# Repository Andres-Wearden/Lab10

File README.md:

## 0 Repository Structure

The typical explanation for the repo structure. Lab specific instructions can be
found further below.

### 0.1 HW

The `hw` folder should contain your schematic and board files for your PCB or
circuits. In labs 1-5 and 10, you will be creating schematics for your circuit
in KiCad. 

### 0.2 SW

The `sw` folder should contain your application firmware and software written
for the lab. The `sw/inc` folder contains firmware drivers written for you by
Professor Valvano. Feel free to write your own (in fact, in some labs, you may
be required to write your own).

You can place any other source files in the `sw` folder. TAs will look at the
files you create and/or modify for software quality and for running your
project.

### 0.3 Resources

A couple files are provided in the Resources folder so you don't have to keep
searching for that one TI document. Some of them are immediately useful, like
the TM4C datasheet. Others may be useful for your final project, like the
TM4C_System_Design_Guidelines page.

### 0.4 Git and Github

We will extensively use Git and Github for managing lab projects. This makes it
easier for TAs to grade and help debug the project by allowing us to see commit
histories, maintain a common project structure, and likewise, it makes it easier
for students to collaborate with partners, merge different codebases, and to
debug their work by having a history of commits.

Two common ways of using Git and Github are [Github Desktop](https://desktop.github.com/) and the [command line](https://git-scm.com/downloads).
[Tutorials](https://dev.to/mollynem/git-github--workflow-fundamentals-5496) are also abundant on the net for you to peruse. We've provided a cheatsheet for git
in the Resources folder.

It is highly recommended to make the most out of Git, even if you've never used
it before. Version control will save you a lot of suffering, and tools like Git
or SVN are ubiquitous in the industry.

A gitignore file is added to the root of this repo that may prevent specific
files from being tagged to the repo. This are typically autogenerated output
files we don't care about, but sometimes other stuff (like .lib files) falls
through that we want. Feel free to modify if necessary.

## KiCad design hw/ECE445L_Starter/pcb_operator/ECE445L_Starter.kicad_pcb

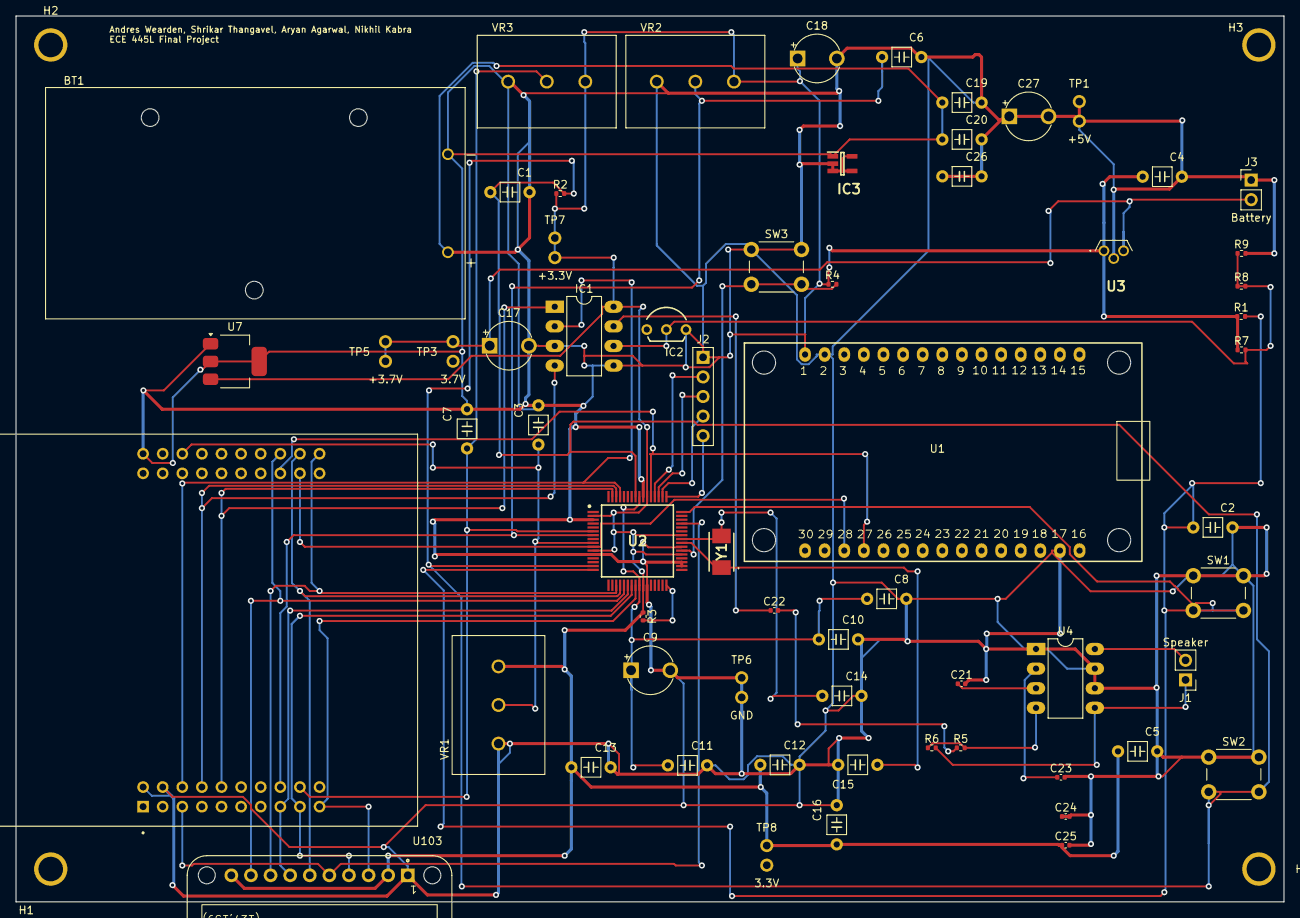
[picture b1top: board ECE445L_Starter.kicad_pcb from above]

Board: 2 copper layers, 164.2 x 114.8 mm, 67 parts (0 on the bottom side), 39 nets.

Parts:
BT1: BH9VPC; BAT_BH9VPC
C1, C2: C; C_Axial_200mil
C3, C5, C6, C7, C10, C11, C12: 0.1uF; C_Axial_200mil
C4, C13: 0.01uF; C_Axial_200mil
C8, C16: 1uF; C_Axial_200mil
C9: 2.2uF; CP_Radial_Tantal200mil
C14, C15: 10pF C0G; C_Axial_200mil
C17, C18, C27: 4.7uF; CP_Radial_Tantal200mil
C19, C20, C26: 1u; C_Axial_200mil
C21: 1uF; C_0402_1005Metric
C22, C24, C25: 100nF; C_0402_1005Metric
C23: 4.7uF; C_0402_1005Metric
H1, H2, H3, H4: MountingHole_4_40
IC1: TLV5616; DIP-8_W7.62mm_LongPads
IC2: LM4041CILPR; ti_LM4041CILPR
IC3: MCP1755T-5002E_OT; SOT95P270X145-5N
J1: Speaker; PinHeader_1x02_P2.54mm_Vertical
J2: JTAG; PinHeader_1x05_P2.54mm_Vertical
J3: Battery; PinHeader_1x02_P2.54mm_Vertical
R1, R2: 10K; R_0402_1005Metric
R3: 1M; R_0402_1005Metric
R4: 10k; R_0402_1005Metric
R5: 20k; R_0402_1005Metric
R6: 110k; R_0402_1005Metric
R7: 500; R_0402_1005Metric
R8: 10.3k; R_0402_1005Metric
R9: 1.425k; R_0402_1005Metric
SW1: UP; SW_PUSH_6mm
SW2: DOWN; SW_PUSH_6mm
SW3: Reset; SW_PUSH_6mm
TP1: +5V; Testpoint_1x02_P2.54mm
TP3: 3.7V; Testpoint_1x02_P2.54mm
TP5: +3.7V; Testpoint_1x02_P2.54mm
TP6: GND; Testpoint_1x02_P2.54mm
TP7: +3.3V; Testpoint_1x02_P2.54mm
TP8: 3.3V; Testpoint_1x02_P2.54mm
U1: ESP32_30pin
U2: TM4C123GH6PMIR; QFP50P1200X1200X160-64N
U3: LP2950-33LPRE3; TL431CLPM
U4: MCP34119P; DIP-8_W7.62mm_LongPads
U5: EK-TM4C123GXL; ti_EKTM4C123GXL
U7: LM2937xMP; SOT-223-3_TabPin2
U103: Adafruit ST7735R; adafruit_st7735r2
VR1, VR2, VR3: P160KN-0QC15B500K; P160
Y1: ABM3-16.000MHZ-B2-T; ABM3

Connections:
+3V3: C4.1, C5.1, C12.1, C13.1, C16.1, C18.1, C25.1, IC1.8 (VDD), R1.1, R2.1, R3.1, R4.1, R7.1, TP7.1 (A), TP7.2 (B), TP8.1, U1.1 (VIN), U2.2 (VDDA), U2.11 (VDD_1), U2.26 (VDD_2), U2.37 (VBAT), U2.42 (VDD_3), U2.54 (VDD_4), U3.1 (OUTPUT), U7.3 (VO), U103.2 (VCC), U103.10 (LITE), VR1.3, VR2.3, VR3.3
+5V: C17.2, C18.2, C20.2, C24.2, C26.1, C26.2, C27.1, C27.2, IC3.5 (VOUT), J3.1 (A), TP1.1 (A), TP1.2 (B), TP6.1 (A), TP6.2 (B), U3.2 (GND), U4.6 (Vcc), U5.J3_1 (+VBUS), U7.1 (VI)
/12V: BT1.+, C19.1, IC3.1 (VIN), IC3.3 (~SHDN)
/+3_7V: C17.1, J3.2 (B), TP3.1, TP5.1 (A), TP5.2 (B), U3.3 (INPUT)
/LDO: C8.1, C9.1, C10.1, C11.1, U2.25 (VDDC_1), U2.56 (VDDC_2)
/OSC1: C14.1, U2.41 (OSC1), Y1.2
/OSC2: C15.1, U2.40 (OSC0), Y1.1
/Reset: R4.2, SW3.2, U2.38 (~RST)
/TCK: J2.2 (B), U2.52 (PC0/TCK/SWCLK)
/TDI: J2.4 (C), U2.50 (PC2/TDI)
/TDO: J2.5 (C), U2.49 (PC3/TDO/SWO)
/TMS: J2.3 (C), U2.51 (PC1/TMS/SWDIO)
DAC_Out: C22.1, IC1.7 (OUT)
GND: BT1.-, C1.2, C2.2, C3.2, C4.2, C5.2, C6.2, C7.2, C8.2, C9.2, C10.2, C11.2, C12.2, C13.2, C14.2, C15.2, C16.2, C19.2, C21.2, C23.2, C24.1, C25.2, IC1.3 (~CS), IC1.5 (AGND), IC2.3, IC3.2 (GND), J2.1 (A), R9.2, SW1.1, SW2.1, SW3.1, U1.2 (GND), U1.17 (GND), U2.3 (GNDA), U2.12 (GND_1), U2.27 (GND_2), U2.34 (XOSC0), U2.35 (GNDX), U2.39 (GND_3), U2.55 (GND_4), U4.1 (CD), U4.7 (GND), U5.J2_1 (GND), U5.J3_2 (GND), U7.2 (GND), U103.1 (GND), VR1.1, VR2.1, VR3.1
unnamed: C22.2, R5.1
unnamed: IC1.6 (REF), IC2.2, R7.2, R8.1, R8.2, R9.1
unnamed: R3.2, U2.32 (~WAKE)
unnamed: C21.1, U4.3 (FC1)
unnamed: C23.1, U4.2 (FC2)
unnamed: R5.2, R6.1, U4.4 (VIN)
unnamed: J1.1, R6.2, U4.5 (VO1)
unnamed: J1.2, U4.8 (VO2)
PA2: U2.19 (PA2/SSI0C1K), U5.J2_10 (PA2), U103.8 (SCK)
PA3: U2.20 (PA3/SSI0FSS), U5.J2_9 (PA3), U103.6 (TFT_CS)
PA4: U2.21 (PA4/SSI0RX), U5.J2_8 (PA4), U103.9 (MISO)
PA5: U2.22 (PA5/SSI0TX), U5.J1_8 (PA5), U103.7 (MOSI)
PA6: U2.23 (PA6), U5.J1_9 (PA6), U103.4 (D/C)
PA7: U2.24 (PA7), U5.J1_10 (PA7), U103.3 (RESET)
PB0: U2.45 (PB0/USB0ID), U5.J1_3 (PB0), U103.5 (CARD_CS)
PB3: C2.1, R1.2, SW1.2, U2.48 (PB3/I2C0SDA)
PB5: C1.1, R2.2, SW2.2, U2.57 (PB5)
PD0: IC1.2 (SCLK), U2.61 (PD0), U5.J3_3 (PD0)
PD1: IC1.4 (FS), U2.62 (PD1), U5.J3_4 (PD1)
PD2: IC1.1 (DIN), U2.63 (PD2), U5.J3_5 (PD2)
PD6: U1.27 (GPIO3), U2.53 (PD6), U5.J4_8 (PD6)
PD7: U1.28 (GPIO1), U2.10 (PD7), U5.J4_9 (PD7)
PE0: C3.1, U2.9 (PE0), U5.J2_3 (PE0), VR1.2
PE2: C6.1, U2.7 (PE2), U5.J3_8 (PE2), VR2.2
PE3: C7.1, U2.6 (PE3), U5.J3_9 (PE3), VR3.2

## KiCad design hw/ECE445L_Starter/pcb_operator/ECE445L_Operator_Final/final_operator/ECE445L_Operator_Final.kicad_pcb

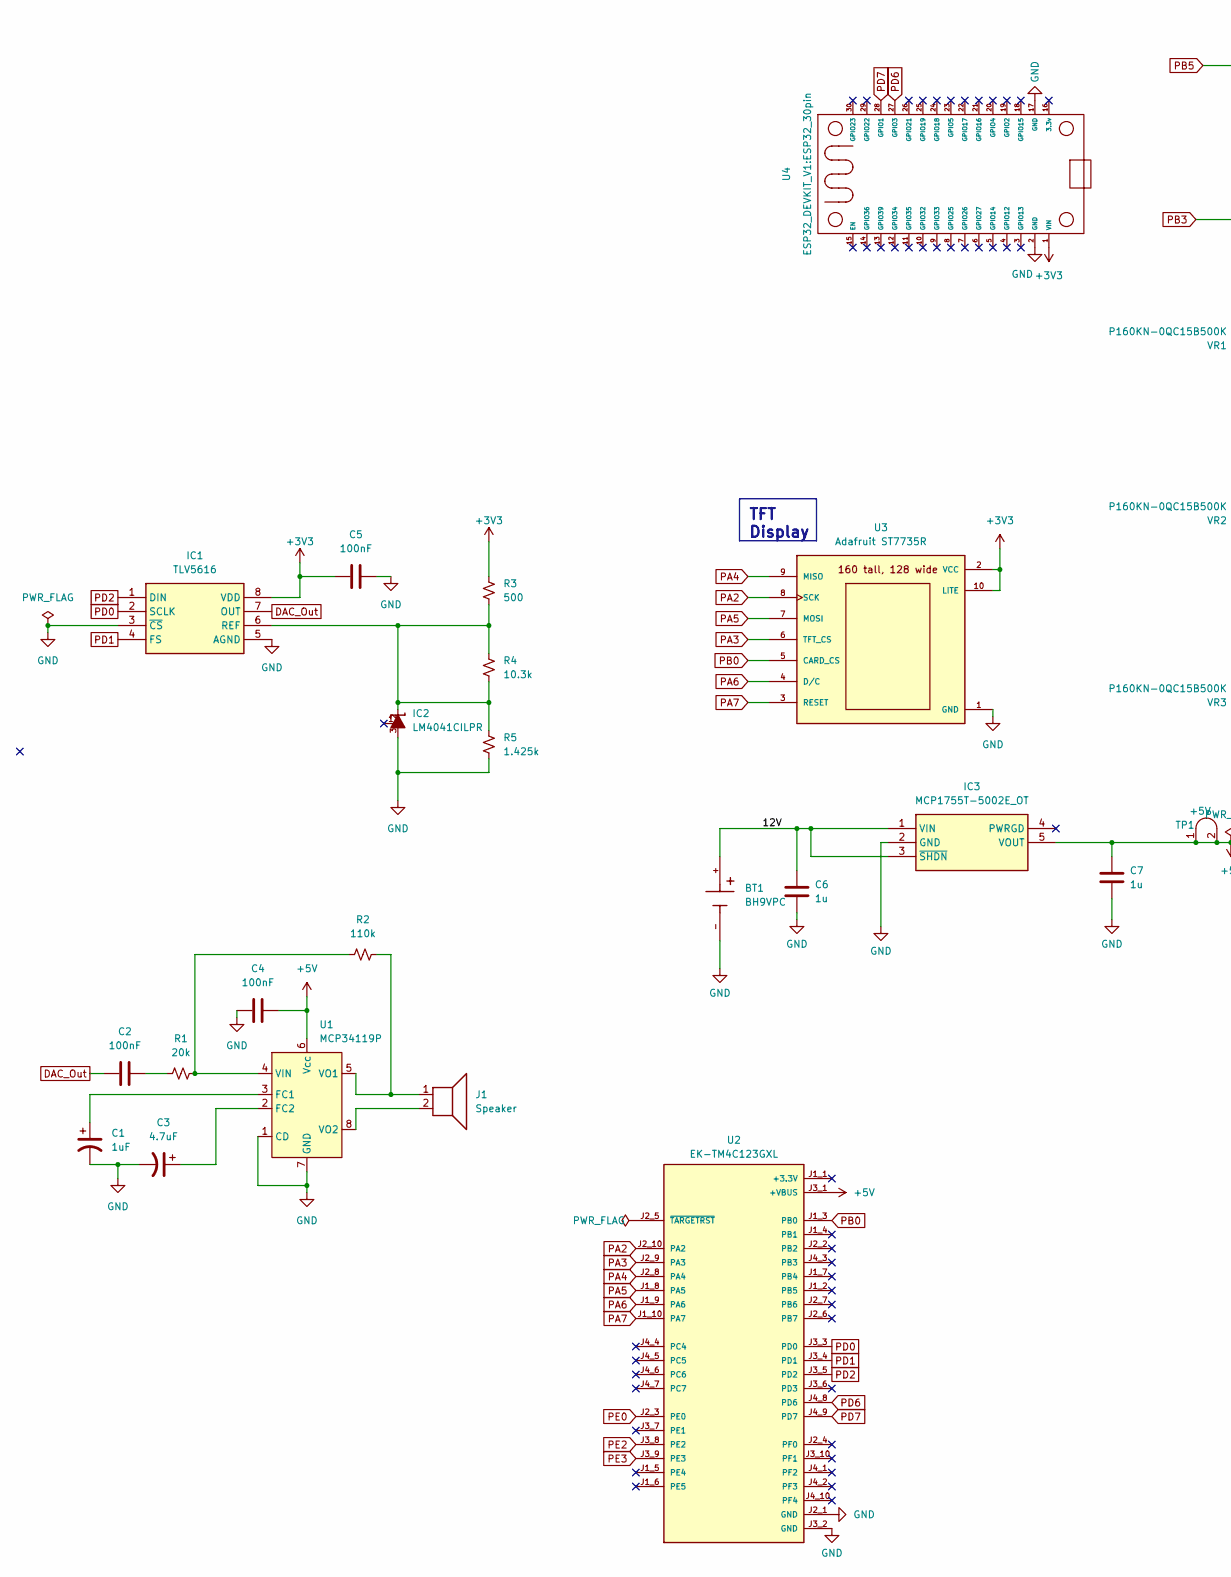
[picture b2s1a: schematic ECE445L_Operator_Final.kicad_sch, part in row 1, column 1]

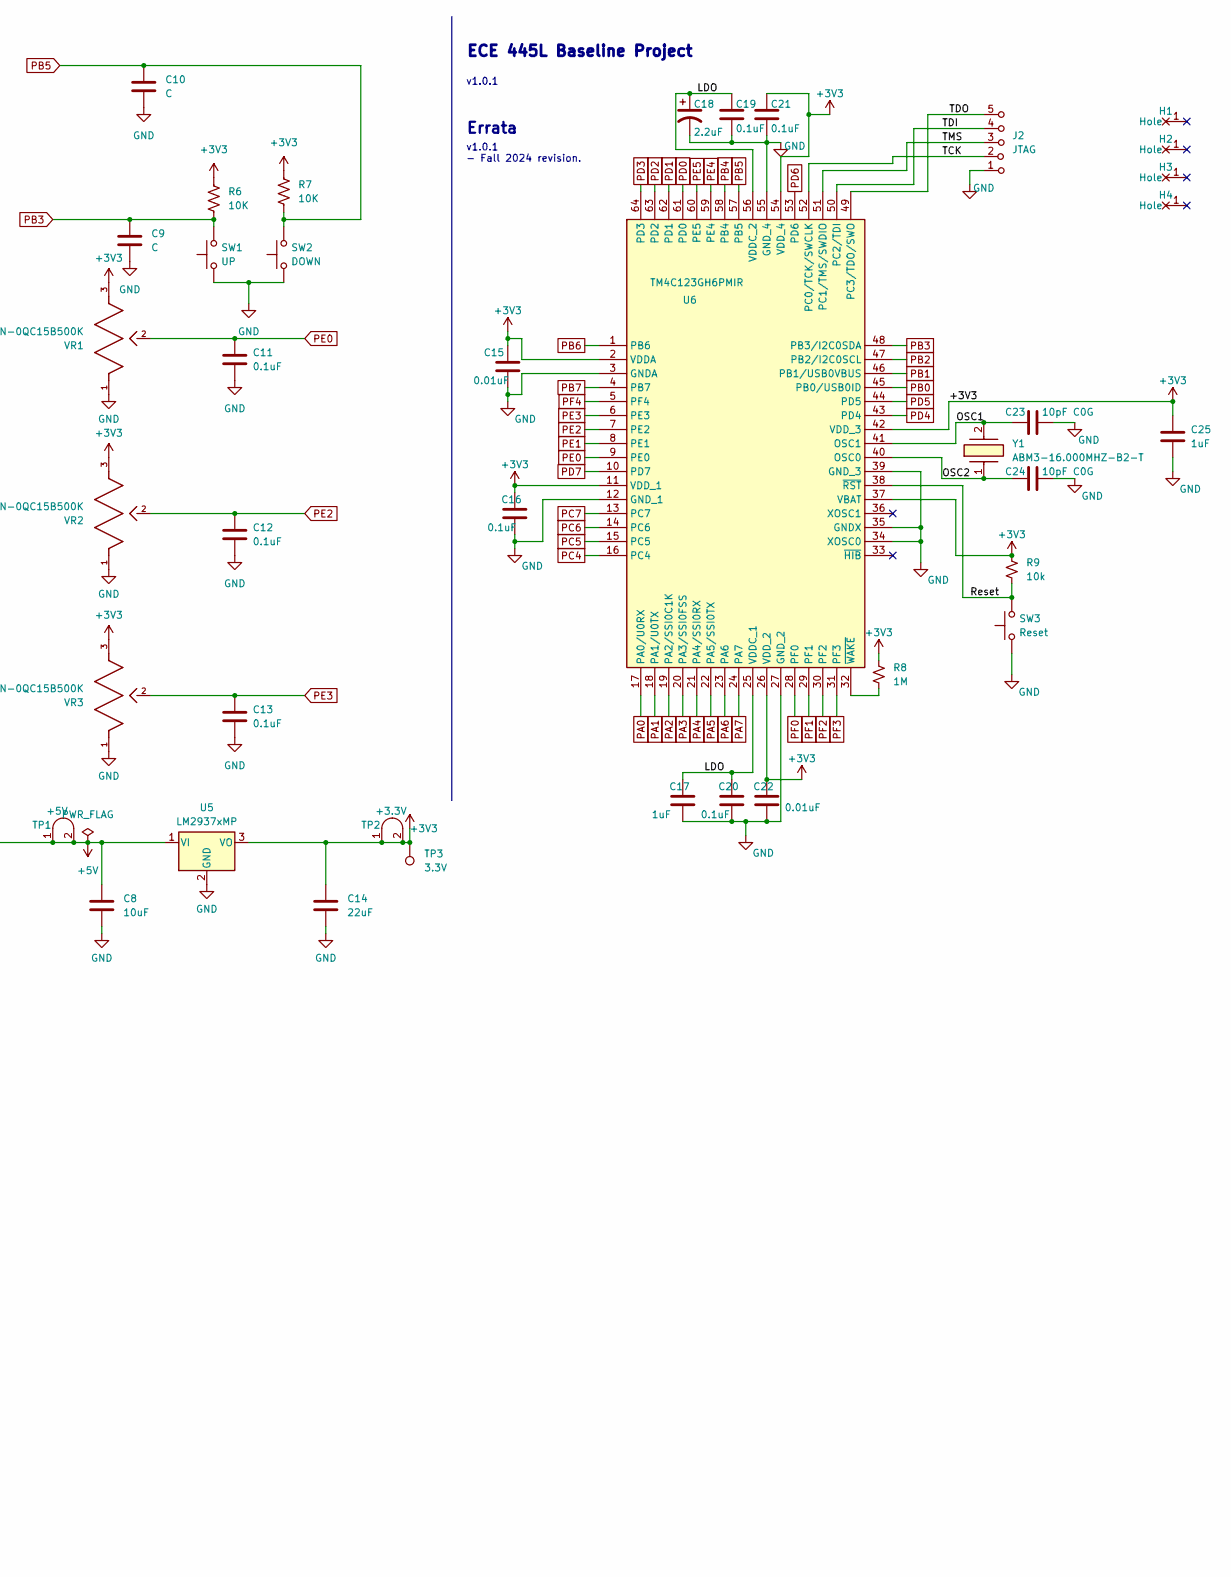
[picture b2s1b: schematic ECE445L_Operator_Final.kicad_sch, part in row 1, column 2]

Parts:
BT1: BH9VPC; BAT_BH9VPC; PARTREV F
C1, C17, C25: 1uF; C_Axial_200mil
C2, C4, C5: 100nF; C_Axial_200mil
C3: 4.7uF; C_Axial_200mil
C6, C7: 1u; C_Axial_200mil
C8: 10uF; C_Axial_200mil
C9, C10: C; C_Axial_200mil
C11, C12, C13, C16, C19, C20, C21: 0.1uF; C_Axial_200mil
C14: 22uF; C_Axial_200mil
C15, C22: 0.01uF; C_Axial_200mil
C18: 2.2uF; C_Axial_200mil
C23, C24: 10pF C0G; C_Axial_200mil
H1, H2, H3, H4: MountingHole_4_40
IC1: TLV5616; DIP-8_W7.62mm_LongPads
IC2: LM4041CILPR; ti_LM4041CILPR
IC3: MCP1755T-5002E_OT; SOT95P270X145-5N; Mouser Part Number 579-MCP1755T-5002EOT
J1: Speaker; PinHeader_1x02_P2.54mm_Vertical
J2: JTAG; PinHeader_1x05_P2.54mm_Vertical
R1: 20k; R_0805_2012Metric
R2: 110k; R_0805_2012Metric
R3: 500; R_0805_2012Metric
R4: 10.3k; R_0805_2012Metric
R5: 1.425k; R_0805_2012Metric
R6, R7: 10K; R_0805_2012Metric
R8: 1M; R_0805_2012Metric
R9: 10k; R_0805_2012Metric
SW1: UP; SW_PUSH_6mm
SW2: DOWN; SW_PUSH_6mm
SW3: Reset; SW_PUSH_6mm
TP1: +5V; Testpoint_1x02_P2.54mm
TP2: +3.3V; Testpoint_1x02_P2.54mm
TP3: 3.3V; Testpoint_1x02_P2.54mm
U1: MCP34119P; DIP-8_W7.62mm_LongPads
U2: EK-TM4C123GXL; ti_EKTM4C123GXL
U3: Adafruit ST7735R; adafruit_st7735r2
U4: ESP32_30pin
U5: LM2937xMP; SOT-223-3_TabPin2
U6: TM4C123GH6PMIR; QFP50P1200X1200X160-64N; Mouser Part Number 595-TM4C123GH6PMIR
VR1: P160KN-0QC15B500K; P160; PARTNO 987-1304-ND
VR2, VR3: P160KN-0QC15B500K; PinHeader_1x03_P2.54mm_Vertical; PARTNO 987-1304-ND
Y1: ABM3-16.000MHZ-B2-T; ABM3; Mouser Part Number 815-ABM3-16-B2-T

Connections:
+3V3: C5.1, C14.1, C15.1, C16.1, C21.1, C22.1, C25.1, IC1.8 (VDD), R3.1, R6.1, R7.1, R8.1, R9.1, TP2.1 (A), TP2.2 (B), TP3.1, U3.2 (VCC), U3.10 (LITE), U4.1 (VIN), U5.3 (VO), U6.2 (VDDA), U6.11 (VDD_1), U6.26 (VDD_2), U6.37 (VBAT), U6.42 (VDD_3), U6.54 (VDD_4), VR1.3, VR2.3, VR3.3
+5V: C4.2, C7.1, C8.1, IC3.5 (VOUT), TP1.1 (A), TP1.2 (B), U1.6 (Vcc), U2.J3_1 (+VBUS), U5.1 (VI)
/12V: BT1.+, C6.1, IC3.1 (VIN), IC3.3 (~SHDN)
/LDO: C17.1, C18.1, C19.1, C20.1, U6.25 (VDDC_1), U6.56 (VDDC_2)
/OSC1: C23.1, U6.41 (OSC1), Y1.2
/OSC2: C24.1, U6.40 (OSC0), Y1.1
/Reset: R9.2, SW3.2, U6.38 (~RST)
/TCK: J2.2 (B), U6.52 (PC0/TCK/SWCLK)
/TDI: J2.4 (C), U6.50 (PC2/TDI)
/TDO: J2.5 (C), U6.49 (PC3/TDO/SWO)
/TMS: J2.3 (C), U6.51 (PC1/TMS/SWDIO)
DAC_Out: C2.1, IC1.7 (OUT)
GND: BT1.-, C1.2, C3.2, C4.1, C5.2, C6.2, C7.2, C8.2, C9.2, C10.2, C11.2, C12.2, C13.2, C14.2, C15.2, C16.2, C17.2, C18.2, C19.2, C20.2, C21.2, C22.2, C23.2, C24.2, C25.2, IC1.3 (~CS), IC1.5 (AGND), IC2.3, IC3.2 (GND), J2.1 (A), R5.2, SW1.1, SW2.1, SW3.1, U1.1 (CD), U1.7 (GND), U2.J2_1 (GND), U2.J3_2 (GND), U3.1 (GND), U4.2 (GND), U4.17 (GND), U5.2 (GND), U6.3 (GNDA), U6.12 (GND_1), U6.27 (GND_2), U6.34 (XOSC0), U6.35 (GNDX), U6.39 (GND_3), U6.55 (GND_4), VR1.1, VR2.1, VR3.1
unnamed: C2.2, R1.1
unnamed: IC1.6 (REF), IC2.2, R3.2, R4.1, R4.2, R5.1
unnamed: C1.1, U1.3 (FC1)
unnamed: C3.1, U1.2 (FC2)
unnamed: R1.2, R2.1, U1.4 (VIN)
unnamed: J1.1, R2.2, U1.5 (VO1)
unnamed: J1.2, U1.8 (VO2)
unnamed: R8.2, U6.32 (~WAKE)
PA0: U6.17 (PA0/U0RX)
PA1: U6.18 (PA1/U0TX)
PA2: U2.J2_10 (PA2), U3.8 (SCK), U6.19 (PA2/SSI0C1K)
PA3: U2.J2_9 (PA3), U3.6 (TFT_CS), U6.20 (PA3/SSI0FSS)
PA4: U2.J2_8 (PA4), U3.9 (MISO), U6.21 (PA4/SSI0RX)
PA5: U2.J1_8 (PA5), U3.7 (MOSI), U6.22 (PA5/SSI0TX)
PA6: U2.J1_9 (PA6), U3.4 (D/C), U6.23 (PA6)
PA7: U2.J1_10 (PA7), U3.3 (RESET), U6.24 (PA7)
PB0: U2.J1_3 (PB0), U3.5 (CARD_CS), U6.45 (PB0/USB0ID)
PB1: U6.46 (PB1/USB0VBUS)
PB2: U6.47 (PB2/I2C0SCL)
PB3: C9.1, R6.2, SW1.2, U6.48 (PB3/I2C0SDA)
PB4: U6.58 (PB4)
PB5: C10.1, R7.2, SW2.2, U6.57 (PB5)
PB6: U6.1 (PB6)
PB7: U6.4 (PB7)
PC4: U6.16 (PC4)
PC5: U6.15 (PC5)
PC6: U6.14 (PC6)
PC7: U6.13 (PC7)
PD0: IC1.2 (SCLK), U2.J3_3 (PD0), U6.61 (PD0)
PD1: IC1.4 (FS), U2.J3_4 (PD1), U6.62 (PD1)
PD2: IC1.1 (DIN), U2.J3_5 (PD2), U6.63 (PD2)
PD3: U6.64 (PD3)
PD4: U6.43 (PD4)
PD5: U6.44 (PD5)
PD6: U2.J4_8 (PD6), U4.27 (GPIO3), U6.53 (PD6)
PD7: U2.J4_9 (PD7), U4.28 (GPIO1), U6.10 (PD7)
PE0: C11.1, U2.J2_3 (PE0), U6.9 (PE0), VR1.2
PE1: U6.8 (PE1)
PE2: C12.1, U2.J3_8 (PE2), U6.7 (PE2), VR2.2
PE3: C13.1, U2.J3_9 (PE3), U6.6 (PE3), VR3.2
PE4: U6.59 (PE4)
PE5: U6.60 (PE5)
PF0: U6.28 (PF0)
PF1: U6.29 (PF1)
PF2: U6.30 (PF2)
PF3: U6.31 (PF3)
PF4: U6.5 (PF4)

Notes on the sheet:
TFT Display
ECE 445L Baseline Project
v1.0.1 - Fall 2024 revision.
v1.0.1
Errata

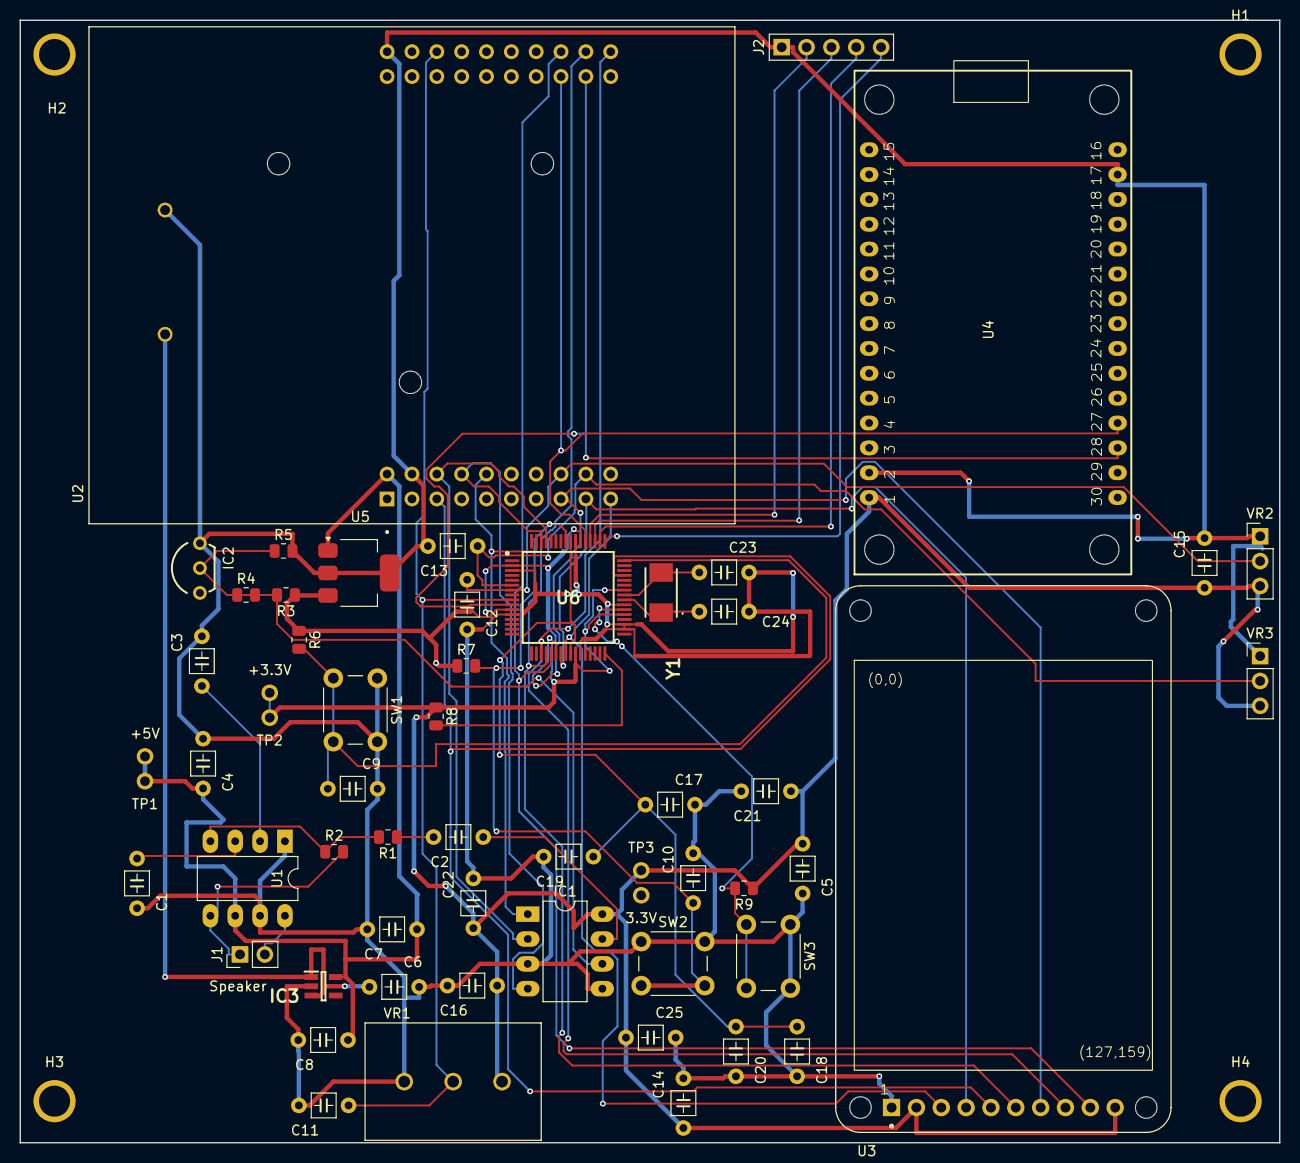
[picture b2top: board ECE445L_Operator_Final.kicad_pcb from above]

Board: 2 copper layers, 128.8 x 114.8 mm, 60 parts (1 on the bottom side), 38 nets.

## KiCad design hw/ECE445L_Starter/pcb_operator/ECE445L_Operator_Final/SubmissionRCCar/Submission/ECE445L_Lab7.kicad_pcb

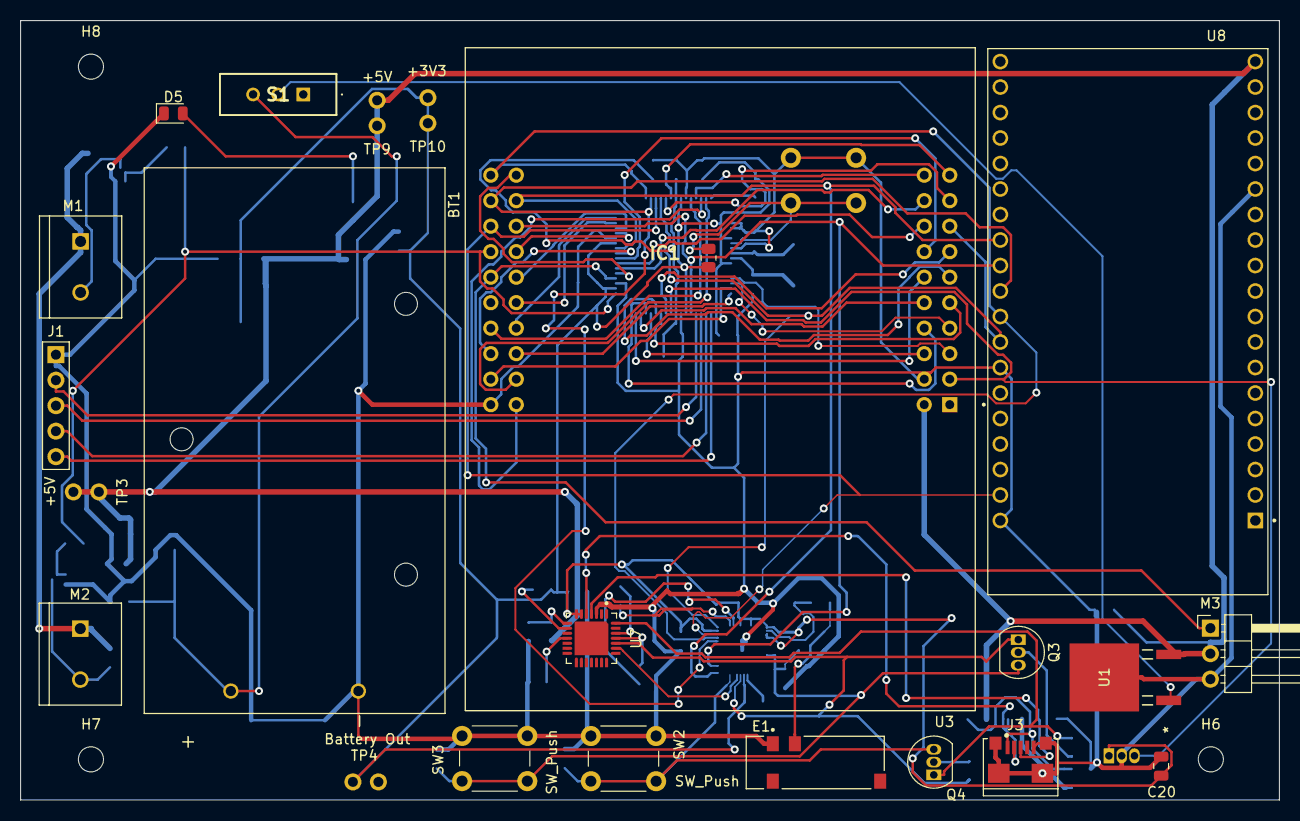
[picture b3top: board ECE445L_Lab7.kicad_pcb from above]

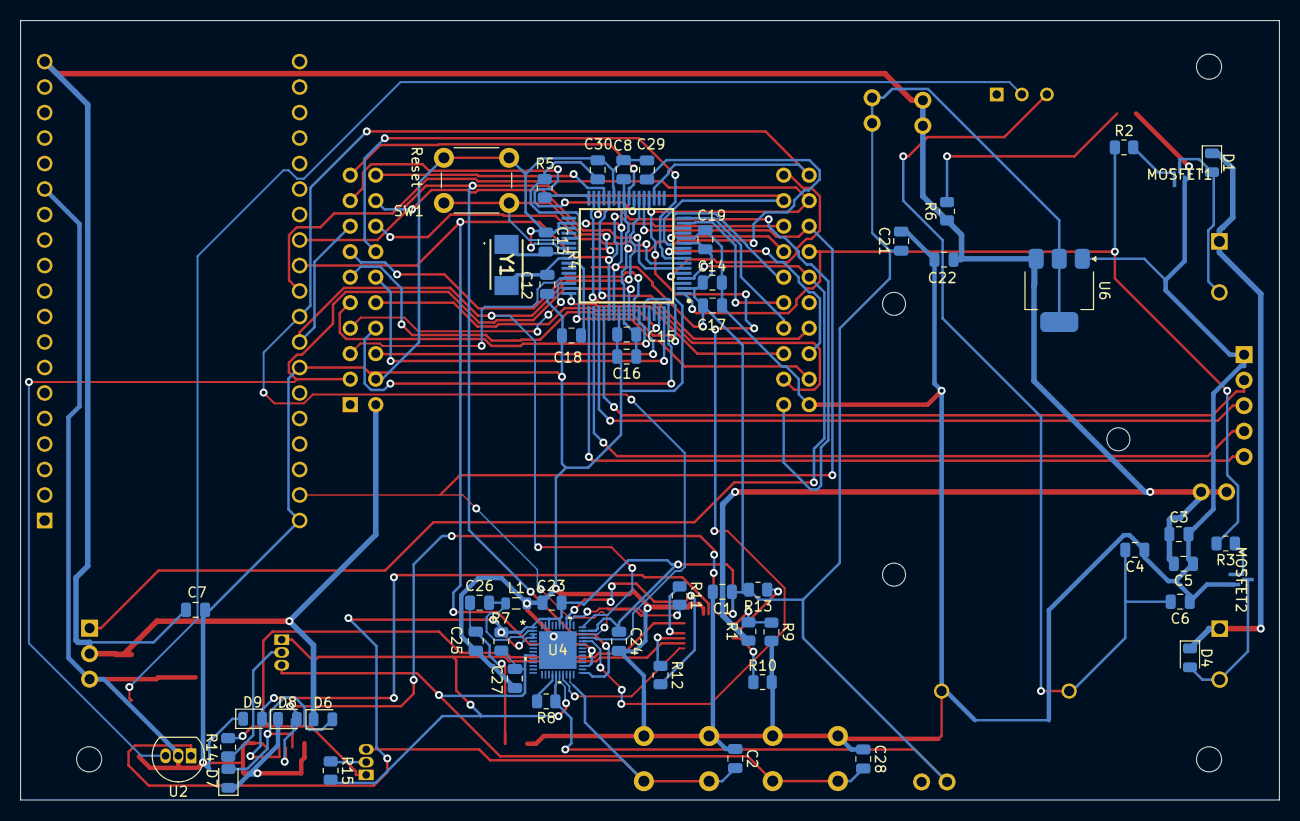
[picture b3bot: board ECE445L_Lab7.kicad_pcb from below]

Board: 2 copper layers, 125.4 x 77.6 mm, 81 parts (55 on the bottom side), 75 nets.

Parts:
BT1: BH9VPC; BAT_BH9VPC
C1, C2, C27, C28: 0.1u; C_0805_2012Metric
C3: 4.7uF; C_0805_2012Metric
C4, C5, C6, C20: 1u; C_0805_2012Metric
C7, C21, C22, C23, C24: 10u; C_0805_2012Metric
C8: 2.2uF; C_0805_2012Metric
C12, C13: 10pF COG; C_0805_2012Metric
C14, C15: 1uF; C_0805_2012Metric
C16, C19, C29, C30: 0.1uF; C_0805_2012Metric
C17, C18: 0.01uF; C_0805_2012Metric
C25: 2.7p; C_0805_2012Metric
C26: 4.7p; C_0805_2012Metric
D1, D4, D6: D; D_0805_2012Metric
D5: LED; LED_0805_2012Metric
D7, D8, D9: D_TVS; D_0805_2012Metric
E1: PRO-OB-440; XDCR_PRO-OB-440
H6, H7, H8: MountingHole_2.5mm
IC1: TM4C123GH6PMIR; QFP50P1200X1200X160-64N
J1: JTAG; PinHeader_1x05_P2.54mm_Vertical
J3: DX4R005HJ5R2000; JAE_DX4R005HJ5R2000
L1: 1.6n; L_0805_2012Metric
M1, M2: Motor_DC; TE_282837-2
M3: Motor_Servo; PinHeader_1x03_P2.54mm_Horizontal
MOSFET1, MOSFET2: SSM3K56FS_LF; SSM_TOS
Q3, Q4: S8050; TO-92_Inline
R1: 22.1k; R_0805_2012Metric
R2, R3, R11, R12: 1k; R_0805_2012Metric
R4, R7, R8, R10, R14, R15: 10k; R_0805_2012Metric
R5: 1M; R_0805_2012Metric
R6, R13: 2k; R_0805_2012Metric
R9: 47.5k; R_0805_2012Metric
S1: SLW-116641-5A-S-D; SLW1166415ASD
SW1: Reset; SW_PUSH_6mm
SW2, SW3: SW_Push; SW_PUSH_6mm
TP3, TP9: +5V; Testpoint_1x02_P2.54mm
TP4: Battery Out; Testpoint_1x02_P2.54mm
TP10: +3V3; Testpoint_1x02_P2.54mm
U1: NCV7805BDTRKG; DPAK-3_ONS
U2: DRV5055A2xLPGxQ1; TO-92_Inline
U3: EK-TM4C123GXL; ti_EKTM4C123GXL
U4: ESP32-D0WD-V3; QFN48_ESP32-D0WD-V3_EXP
U6: AMS1117; SOT-223-3_TabPin2
U7: CP2102N-A02-GQFN28R; IC_CP2102N-A02-GQFN28R
U8: ESP32-DEVKITC-32D; MODULE_ESP32-DEVKITC-32D
Y1: ABM3-16.000MHZ-B2-T; ABM3

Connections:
+5V: C3.1, C5.2, C7.1, C22.1, D6.1 (K), M3.2 (+), R1.1, R6.1, TP3.1 (A), TP3.2 (B), TP9.1 (A), TP9.2 (B), U1.3 (OUTPUT), U3.J3_1 (+VBUS), U6.3 (VI), U8.J2-19 (EXT_5V)
+9V: D1.1 (K), D4.1 (K), M1.1 (+), M2.1 (+)
/Lab7_microcontroller/LDO: C8.1, C15.1, C16.1, C29.1, IC1.25 (VDDC_1), IC1.56 (VDDC_2)
/Lab7_microcontroller/OSC1: C12.1, IC1.41 (OSC1), Y1.2
/Lab7_microcontroller/OSC2: C13.1, IC1.40 (OSC0), Y1.1
/Lab7_microcontroller/Reset: IC1.38 (~RST), R4.2, SW1.2
/Lab7_microcontroller/TCK: IC1.52 (PC0/TCK/SWCLK), J1.2 (B)
/Lab7_microcontroller/TDI: IC1.50 (PC2/TDI), J1.4 (C)
/Lab7_microcontroller/TDO: IC1.49 (PC3/TDO/SWO), J1.5 (C)
/Lab7_microcontroller/TMS: IC1.51 (PC1/TMS/SWDIO), J1.3 (C)
/Lab7_power/+9V: BT1.+, C4.2, C6.2, S1.3 (NO)
CTS: U4.21 (MTDO), U7.23 (CTS)
DTR: Q4.1 (E), R14.2, U7.28 (DTR)
EN: C27.1, C28.2, Q3.3 (C), R7.2, SW3.2, U4.9 (CHIP_PU)
GND: BT1.-, C1.2, C2.1, C3.2, C4.1, C5.1, C6.1, C7.2, C8.2, C12.2, C13.2, C14.2, C15.2, C16.2, C17.2, C18.2, C19.2, C20.2, C21.2, C22.2, C23.2, C24.2, C25.2, C27.2, C28.1, C29.2, C30.2, D5.1 (K), D7.1 (A1), D8.1 (A1), D9.1 (A1), E1.1, IC1.3 (GNDA), IC1.12 (GND_1), IC1.27 (GND_2), IC1.34 (XOSC0), IC1.35 (GNDX), IC1.39 (GND_3), IC1.55 (GND_4), J1.1 (A), J3.5 (GND), J3.SH1 (SHIELD), J3.SH2 (SHIELD__1), J3.SH3 (SHIELD__2), J3.SH4 (SHIELD__3), L1.2, M3.3 (-), MOSFET1.2, MOSFET2.2, R9.2, R10.2, SW1.1, SW2.1, SW3.1, U1.2 (GROUND), U2.2 (GND), U3.J2_1 (GND), U3.J3_2 (GND), U4.49 (GND), U6.1 (ADJ), U7.3 (GND), U8.J2-14 (GND1), U8.J3-1 (GND3), U8.J3-7 (GND2)
IO0: C2.2, Q4.3 (C), SW2.2, U4.23 (GPIO0)
unnamed: C25.1, C26.1, E1.2
unnamed: D1.2 (A), M1.2 (-), MOSFET1.3
unnamed: D4.2 (A), M2.2 (-), MOSFET2.3
unnamed: D5.2 (A), R6.2
unnamed: D6.2 (A), D7.2 (A2), J3.1 (VBUS)
unnamed: IC1.32 (~WAKE), R5.2
unnamed: MOSFET1.1, R2.2
unnamed: MOSFET2.1, R3.1
unnamed: Q3.2 (B), R14.1
unnamed: Q4.2 (B), R15.1
unnamed: S1.2 (COM), U1.1 (INPUT)
unnamed: C26.2, L1.1, U4.2 (LNA_IN)
unnamed: R8.2, U4.18 (MTDI)
unnamed: R12.1, U7.25 (RXD)
unnamed: R11.1, U7.26 (TXD)
unnamed: R1.2, R9.1, U7.8 (VBUS)
unnamed: R13.1, U7.9 (~RST)
unnamed: R10.1, U7.11 (~SUSPEND)
PA2: IC1.19 (PA2/SSI0C1K), U3.J2_10 (PA2), U4.35 (GPIO18), U8.J3-9 (IO18)
PA3: IC1.20 (PA3/SSI0FSS), U3.J2_9 (PA3), U4.34 (GPIO5), U8.J3-10 (IO5)
PA4: IC1.21 (PA4/SSI0RX), U3.J2_8 (PA4), U4.36 (GPIO23), U8.J3-2 (IO23)
PA5: IC1.22 (PA5/SSI0TX), U3.J1_8 (PA5), U4.38 (GPIO19), U8.J3-8 (IO19)
PA6: IC1.23 (PA6), U3.J1_9 (PA6)
PA7: IC1.24 (PA7), U3.J1_10 (PA7)
PB0: IC1.45 (PB0/USB0ID), U3.J1_3 (PB0)
PB1: IC1.46 (PB1/USB0VBUS), U3.J1_4 (PB1)
PB2: IC1.47 (PB2/I2C0SCL), U3.J2_2 (PB2)
PB3: IC1.48 (PB3/I2C0SDA), U3.J4_3 (PB3)
PB4: IC1.58 (PB4), U3.J1_7 (PB4)
PB5: IC1.57 (PB5), U2.3 (OUT), U3.J1_2 (PB5)
PB6: IC1.1 (PB6), R2.1, R3.2, U3.J2_7 (PB6)
PB7: IC1.4 (PB7), M3.1 (PWM), U3.J2_6 (PB7)
PC4: IC1.16 (PC4), U3.J4_4 (PC4)
PC5: IC1.15 (PC5), U3.J4_5 (PC5)
PC6: IC1.14 (PC6), U3.J4_6 (PC6)
PC7: IC1.13 (PC7), U3.J4_7 (PC7)
PD0: IC1.61 (PD0), U3.J3_3 (PD0)
PD1: IC1.62 (PD1), U3.J3_4 (PD1)
PD2: IC1.63 (PD2), U3.J3_5 (PD2)
PD3: IC1.64 (PD3), U3.J3_6 (PD3)
PD6: IC1.53 (PD6), U3.J4_8 (PD6), U4.27 (GPIO17), U8.J3-11 (IO17)
PD7: IC1.10 (PD7), U3.J4_9 (PD7), U4.25 (GPIO16), U8.J3-12 (IO16)
PE0: IC1.9 (PE0), U3.J2_3 (PE0)
PE1: IC1.8 (PE1), U3.J3_7 (PE1)
PE2: IC1.7 (PE2), U3.J3_8 (PE2)
PE3: IC1.6 (PE3), U3.J3_9 (PE3)
PE4: IC1.59 (PE4), U3.J1_5 (PE4)
PE5: IC1.60 (PE5), U3.J1_6 (PE5)
PF0: IC1.28 (PF0), U3.J2_4 (PF0)
PF1: IC1.29 (PF1), U3.J3_10 (PF1)
PF2: IC1.30 (PF2), U3.J4_1 (PF2)
PF3: IC1.31 (PF3), U3.J4_2 (PF3)
PF4: IC1.5 (PF4), U3.J4_10 (PF4)
REGIN: C1.1, C14.1, C17.1, C18.1, C19.1, C20.1, C21.1, C23.1, C24.1, C30.1, IC1.2 (VDDA), IC1.11 (VDD_1), IC1.26 (VDD_2), IC1.37 (VBAT), IC1.42 (VDD_3), IC1.54 (VDD_4), R4.1, R5.1, R7.1, R8.1, R13.2, TP4.1, TP10.1 (A), TP10.2 (B), U2.1 (VCC), U4.1 (VDDA), U4.3 (VDD3P3), U4.4 (VDD3P3), U4.19 (VDD3P3_RTC), U4.37 (VDD3P3_CPU), U4.43 (VDDA), U4.46 (VDDA), U6.2 (VO), U7.6 (VDD), U7.7 (VREGIN)
RTS: Q3.1 (E), R15.2, U4.20 (MTCK), U7.24 (RTS)
RXD0: R11.2, U4.40 (U0RXD)
TXD0: R12.2, U4.41 (U0TXD)
USB_DN: D8.2 (A2), J3.2 (D_M), U7.5 (D-)
USB_DP: D9.2 (A2), J3.3 (D_P), U7.4 (D+)

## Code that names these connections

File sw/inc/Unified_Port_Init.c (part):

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// Port A drives the ST7735 LCD 
//
// Backlight (pin 10) connected to +3.3 V
// MISO      (pin 9)  connected to PA4
// SCK       (pin 8)  connected to PA2 (SSI0Clk)
// MOSI      (pin 7)  connected to PA5 (SSI0Tx)
// TFT_CS    (pin 6)  connected to PA3 (SSI0Fss)
// CARD_CS   (pin 5)  connected to PB0 (GPIO)
// Data/CMD  (pin 4)  connected to PA6 (GPIO), high for data, low for command
// RESET     (pin 3)  connected to PA7 (GPIO)
// VCC       (pin 2)  connected to +3.3 V
// Gnd       (pin 1)  connected to ground
//
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  SYSCTL_RCGCGPIO_R     |= 0x01;            // Activate port A
  while((SYSCTL_PRGPIO_R & 0x01)==0){};     // allow time for clock to start
    
  GPIO_PORTA_DIR_R      |= 0xC8;            // make PA3,6,7 out
  GPIO_PORTA_AFSEL_R    &= ~0xC8;           // disable alt funct on PA3,6,7
  GPIO_PORTA_DEN_R      |= 0xC8;            // enable digital I/O on PA3,6,7
  
  // configure PA3,6,7 as GPIO
  GPIO_PORTA_PCTL_R      = (GPIO_PORTA_PCTL_R
                         & 0x00FF0FFF)
                         + 0x00000000;
  
  GPIO_PORTA_AMSEL_R    &= ~0xC8;           // disable analog functionality on PA3,6,7

  // initialize SSI0
  GPIO_PORTA_AFSEL_R    |= 0x2C;            // enable alt funct on PA2,3,5
  GPIO_PORTA_DEN_R      |= 0x2C;            // enable digital I/O on PA2,3,5
 
  // configure PA2,3,5 as SSI
  GPIO_PORTA_PCTL_R      = (GPIO_PORTA_PCTL_R
                         & 0xFF0F00FF)
                         + 0x00202200;
  
  GPIO_PORTA_AMSEL_R    &= ~0x2C;           // disable analog functionality on PA2,3,5
  SSI0_CR1_R            &= ~SSI_CR1_SSE;    // disable SSI
  SSI0_CR1_R            &= ~SSI_CR1_MS;     // master mode
  
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// ----------------    PORT B Initialization   --------------------------------
// ----------------------------------------------------------------------------
//
// PB7 = PWM Ouptut to JP6 (M0PWM1)
// PB6 = PWM Output to Motor (M0PWM0)
// PB5 = ADC Input (AIN11)
// PB4 = Timer Capture input (T1CCP0)
// PB3 = GPIO 
// PB2 = GPIO/I2C0
// PB1 = GPIO/I2C0CL
// PB0 = ST7735 Card CS

void Port_B_Init(void){ 
  
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  SYSCTL_RCGCGPIO_R     |= 0x02;            // activate port B
  while((SYSCTL_PRGPIO_R & 0x02) == 0){};   // Wait
  
  // ---------------  Initialize PB7 as M0PWM1  -----------------------  

  GPIO_PORTB_AFSEL_R    |=  0x80;           // enable alt funct on PB7
  GPIO_PORTB_PCTL_R     &= ~0xF0000000;     // configure PB7 as M0PWM1
  GPIO_PORTB_PCTL_R     |=  0x40000000;
  GPIO_PORTB_AMSEL_R    &= ~0x80;           // disable analog functionality on PB7
  GPIO_PORTB_DEN_R      |=  0x80;           // enable digital I/O on PB7

  // ---------------  Initialize PB6 as M0PWM0  -----------------------
  GPIO_PORTB_AFSEL_R    |=  0x40;           // enable alt funct on PB6
  GPIO_PORTB_PCTL_R     &= ~0x0F000000;     // configure PB6 as PWM0
  GPIO_PORTB_PCTL_R     |=  0x04000000;  
  GPIO_PORTB_AMSEL_R    &= ~0x40;           // disable analog functionality on PB6
  GPIO_PORTB_DEN_R      |=  0x40;           // enable digital I/O on PB6
  
  // ---------------  Initialize PB5 as AIN11  ----------------------- 
  GPIO_PORTB_DIR_R      &= ~0x20;           // make PB5 input
  GPIO_PORTB_AFSEL_R    |=  0x20;           // enable alternate function on PB5
  GPIO_PORTB_DEN_R      &= ~0x20;           // disable digital I/O on PB5
  GPIO_PORTB_AMSEL_R    |=  0x20;           // enable analog functionality on PB5

  // ----------------- Initialize PB4 as Timer Capture input (T1CCP0) ---------
  GPIO_PORTB_DIR_R      &= ~0x10;           // make PB4 input
  GPIO_PORTB_AFSEL_R    |= 0x10;            // enable alt funct on PB4
  GPIO_PORTB_DEN_R      |= 0x10;            // enable digital I/O on PB4
                                            // configure PB4 (T1CCP0)
  GPIO_PORTB_PCTL_R     = (GPIO_PORTB_PCTL_R 
                        &  0xFFF0FFFF)
                        +  0x00070000;
  GPIO_PORTB_AMSEL_R    &= ~0x10;           // disable analog functionality on PB4

  // ----------------- Initialize PB3-0 as GPIO ---------
                                      
  GPIO_PORTB_PCTL_R     &= ~0x0000FFFF;     // GPIO
  GPIO_PORTB_DIR_R      |=  0x0F;           // make PB3-0 out
  GPIO_PORTB_AFSEL_R    &= ~0x0F;           // regular port function
  GPIO_PORTB_DEN_R      |=  0x0F;           // enable digital I/O on PB3-0
  GPIO_PORTB_AMSEL_R    &= ~0x0F;           // disable analog functionality on PB3-0
  
  
  }
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// ----------------    PORT C Initialization   --------------------------------
// ----------------------------------------------------------------------------
//
// PC4 = UP switch
// PC5 = RIGHT switch
// PC6 = LEFT switch
// PC7 = DOWN switch
//

void Port_C_Init(void){ 
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   
  GPIO_PORTC_PCTL_R     &= ~0xFFFF0000;   // regular GPIO
  GPIO_PORTC_AMSEL_R    &= ~0xF0;         // disable analog function 
  GPIO_PORTC_DIR_R      &= ~0xF0;         // inputs on PC7-PC4
  GPIO_PORTC_AFSEL_R    &= ~0xF0;         // regular port function
  GPIO_PORTC_PUR_R       =  0xF0;         // enable pull-up on PC7-PC4
  GPIO_PORTC_DEN_R      |=  0xF0;         // enable digital port 
  }  
  
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// ----------------    PORT D Initialization   --------------------------------
// ----------------------------------------------------------------------------
//
// PD7 = U2TX
// PD6 = U2RX
// PD3 = SSI1_MOSI  (to TLV5616)
// PD2 = AIN5 (Monitor DAC_OUT signal from TLV5616)
// PD1 = SSI1_FS/CS (to TLV5616)
// PD0 = SSI1_SCK   (to TLV5616)
  
void Port_D_Init(void){
 
  SYSCTL_RCGCGPIO_R     |= 0x08;            // activate port D
  while((SYSCTL_PRGPIO_R & 0x08)==0){};     // allow time for clock to stabilize

  // ---------------  Initialize PB7 as U2TX, PB6 as U2RX  -----------------------  
    
  GPIO_PORTD_LOCK_R      = 0x4C4F434B;      // unlock REQUIRED for PD7
  GPIO_PORTD_CR_R       |= 0xC0;            // commit PD6, PD7
  
  GPIO_PORTD_AMSEL_R    &= ~0xC0;           // disable analog functionality on PD6, PD7
  GPIO_PORTD_AFSEL_R    |=  0xC0;           // enable alternate function on PD6, PD7
  GPIO_PORTD_DEN_R      |=  0xC0;           // enable digital on PD6, PD7 (PD6 is U2RX, PD7 is U2TX)
  GPIO_PORTD_PCTL_R      =(GPIO_PORTD_PCTL_R  
                         & 0x00FFFFFF)
                         | 0x11000000;      // configure PD6, PD7 as UART
 
   // ---------------  Initialize PD2 as AIN5  ----------------------------------  
   
  GPIO_PORTD_DIR_R      &= ~0x04;           // make PD2 input
  GPIO_PORTD_AFSEL_R    |=  0x04;           // enable alternate function on PD2
  GPIO_PORTD_DEN_R      &= ~0x04;           // disable digital I/O on PD2
  GPIO_PORTD_AMSEL_R    |=  0x04;           // enable analog functionality on PD2

  // ---------------  Initialize PD3,1,0 as SSI1 MOSI, FS & SCK  ---------------- 
    
  GPIO_PORTD_AMSEL_R    &= ~0x0B;           // disable analog functionality on PD
  GPIO_PORTD_AFSEL_R    |=  0x0B;           // enable alt funct on PD3,1,0
  GPIO_PORTD_DEN_R      |=  0x0B;           // enable digital I/O on PD3,1,0
  GPIO_PORTD_PCTL_R      = (GPIO_PORTD_PCTL_R
                          & 0xFFFF0F00)
                          + 0x00002022;
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// ----------------    PORT E Initialization   --------------------------------
// ----------------------------------------------------------------------------
//
// PE5 = U5TX
// PE4 = U5RX
// PE3 = Heartbeat LED
// PE2 = AIN_1 (DAC_OUT Monitor)
// PE1 = RSTB_8266
// PE0 = 8266_ GPIO_2 

void Port_E_Init(void){

  SYSCTL_RCGCGPIO_R     |= 0x10;            // activate port E
  while((SYSCTL_PRGPIO_R & 0x10)==0){};

 // ---------------  Initialize PE5 as U5TX, PE4 as U5RX  -----------------------  

  GPIO_PORTE_AFSEL_R    |= 0x30;            // enable alt funct on PE5-4
  GPIO_PORTE_DEN_R      |= 0x30;            // enable digital I/O on PE5-4
                                            // configure PE5-4 as UART
  GPIO_PORTE_PCTL_R      = (GPIO_PORTE_PCTL_R
                         & 0xFF00FFFF)
                         + 0x00110000;
  GPIO_PORTE_AMSEL_R    &= ~0x30;           // disable analog functionality on PE

 // ---------------  Initialize PE3,1,0 as GPIO  ---------------------------------  

  GPIO_PORTE_DIR_R      |=  0x0A;           // output digital I/O on PE3,1
  GPIO_PORTE_DIR_R      &= ~0x01;           // input digital I/O on PE0
  GPIO_PORTE_AMSEL_R    &= ~0x0B;           // disable analog functionality on PE3,1,0
  GPIO_PORTE_AFSEL_R    &= ~0x0B;           // disable alt funct on PE3,1,0
  GPIO_PORTE_DEN_R      |=  0x0B;           // enable digital I/O on PE3,1,0
  
  GPIO_PORTE_PCTL_R      = (GPIO_PORTE_PCTL_R 
                         & 0xFFFF0F00);
  
// ---------------  Initialize PE2 as AIN1  ---------------------------------  
  
  GPIO_PORTE_DIR_R      &= ~0x04;           // make PE2 input
  GPIO_PORTE_AFSEL_R    |=  0x04;           // enable alternate function on PE2
  GPIO_PORTE_DEN_R      &= ~0x04;           // disable digital I/O on PE2
  GPIO_PORTE_AMSEL_R    |=  0x04;           // enable analog functionality on PE2
}
  
// ----------------------------------------------------------------------------
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
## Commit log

2025-03-03 Prepare flatten
2025-03-03 Flatten
2025-03-04 add deadline
2025-03-29 finished
2025-04-24 pedal ADC code to TM4C
2025-04-24 finished all ADCs beginning the motor
2025-04-26 final operator code
